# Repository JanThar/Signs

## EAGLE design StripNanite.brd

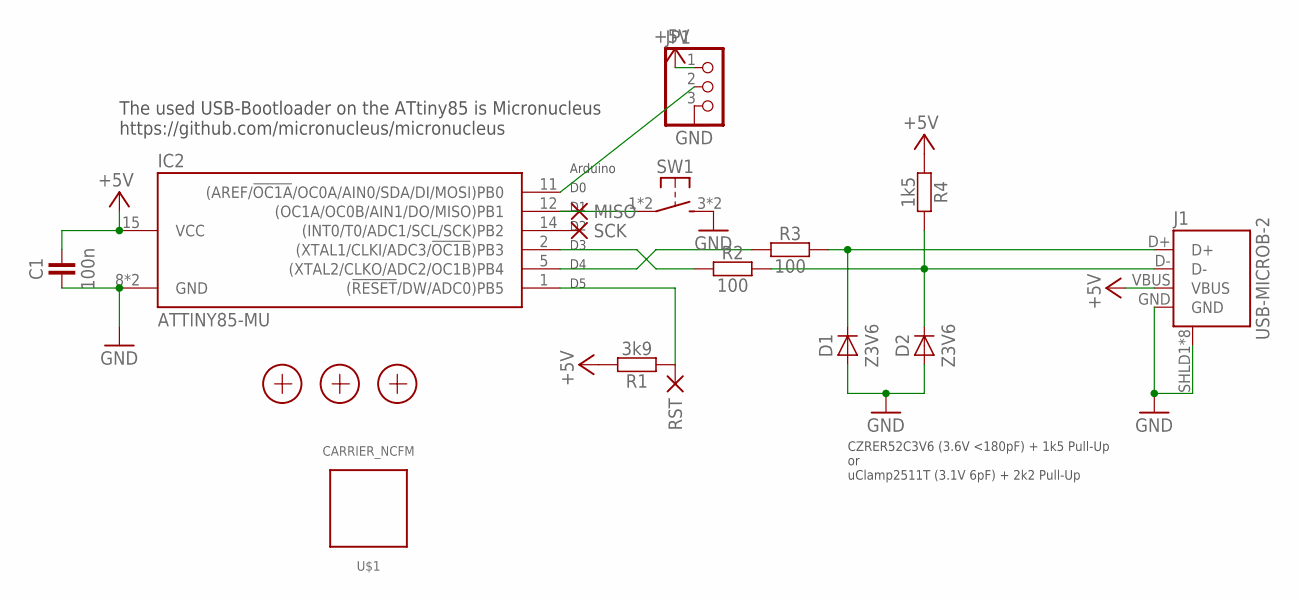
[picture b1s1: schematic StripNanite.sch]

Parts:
C1: 100n; C0402
D1, D2: Z3V6; SOD882
IC2: ATTINY85-MU; QFN20-PAD
J1: USB-MICROB-2; USB-MICROB-10118194
JP1: PINHD-1X3; 1X03
MISO: PAD-1.0
R1: 3k9; C0402
R2, R3: 100; C0402
R4: 1k5; C0402
RST: PAD-1.0
SCK: PAD-1.0
SW1: SW-TACTILE-PTS840P; PTS840P
U$1: CARRIER_NCFM; FM
X1, X2, X3: PASSER-07; PASSER_07MM

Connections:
+5V: C1.2, IC2.15 (VCC), J1.VBUS, JP1.1, R1.2, R4.1
D_P: D1.C, J1.D+, R3.2
GND: C1.1, D1.A, D2.A, IC2.8 (GND), IC2.TP (GND), J1.GND, J1.SHLD1 (SHIELD), J1.SHLD2 (SHIELD), J1.SHLD3 (SHIELD), J1.SHLD4 (SHIELD), J1.SHLD5 (SHIELD), J1.SHLD6 (SHIELD), J1.SHLD7 (SHIELD), J1.SHLD8 (SHIELD), JP1.3, SW1.3 (S1), SW1.4 (S1)
unnamed: IC2.11 ((AREF/!OC1A!/OC0A/AIN0/SDA/DI/MOSI)PB0), JP1.2
unnamed: D2.C, J1.D-, R2.2, R4.2
unnamed: IC2.14 ((INT0/T0/ADC1/SCL/SCK)PB2), SCK.1
unnamed: IC2.12 ((OC1A/OC0B/AIN1/DO/MISO)PB1), MISO.1, SW1.1, SW1.2 (P1)
PB3: IC2.2 ((XTAL1/CLKI/ADC3/!OC1B!)PB3), R2.1
PB4: IC2.5 ((XTAL2/CLKO/ADC2/OC1B)PB4), R3.1
PB5: IC2.1 ((!RESET!/DW/ADC0)PB5), R1.1, RST.1

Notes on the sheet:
The used USB-Bootloader on the ATtiny85 is Micronucleus https://github.com/micronucleus/micronucleus
CZRER52C3V6 (3.6V <180pF) + 1k5 Pull-Up or uClamp2511T (3.1V 6pF) + 2k2 Pull-Up
Arduino

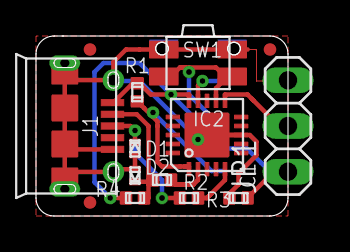
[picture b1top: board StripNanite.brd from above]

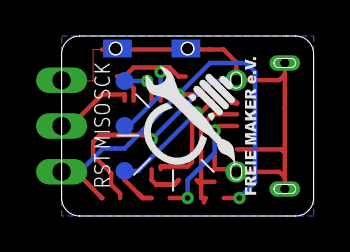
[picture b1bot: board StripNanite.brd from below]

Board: 2 copper layers, 14.0 x 10.0 mm, 18 parts (4 on the bottom side), 10 nets.
